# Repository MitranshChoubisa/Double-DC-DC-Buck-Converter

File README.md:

# Double-DC-DC-Buck-Converter
Design of an 48V to 12V to 5V buck converter using LM2576 IC.

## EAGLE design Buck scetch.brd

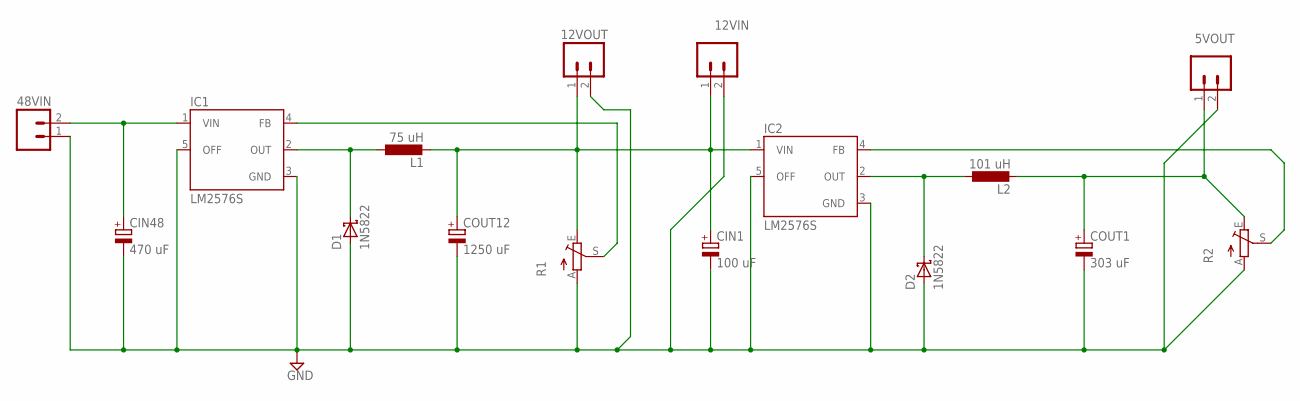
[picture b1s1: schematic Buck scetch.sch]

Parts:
5VOUT, 12VIN, 12VOUT, 48VIN: M02; 02P
CIN1: 100 uF; 140CLH-0810
CIN48: 470 uF; 140CLH-0810
COUT1: 303 uF; 140CLH-0810
COUT12: 1250 uF; 140CLH-0810
D1, D2: 1N5822; DIOAD2120W130L950D530P
IC1, IC2: LM2576S; TO263-5
L1: 75 uH; POWER-CHOKE_WE-TPC
L2: 101 uH; POWER-CHOKE_WE-TPC
R1: 0; B25P
R2: TRIM_EU-B25P; B25P

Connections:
GND: 5VOUT.2, 12VIN.2, 12VOUT.2, 48VIN.1, CIN1.-, CIN48.-, COUT1.-, COUT12.-, D1.A, D2.A, IC1.3 (GND), IC1.5 (OFF), IC2.3 (GND), IC2.5 (OFF), R1.A, R2.A
unnamed: D1.C, IC1.2 (OUT), L1.1
unnamed: 12VIN.1, 12VOUT.1, CIN1.+, COUT12.+, IC2.1 (VIN), L1.2, R1.E
unnamed: IC1.4 (FB), R1.S
unnamed: 48VIN.2, CIN48.+, IC1.1 (VIN)
unnamed: D2.C, IC2.2 (OUT), L2.1
unnamed: 5VOUT.1, COUT1.+, L2.2, R2.E
unnamed: IC2.4 (FB), R2.S

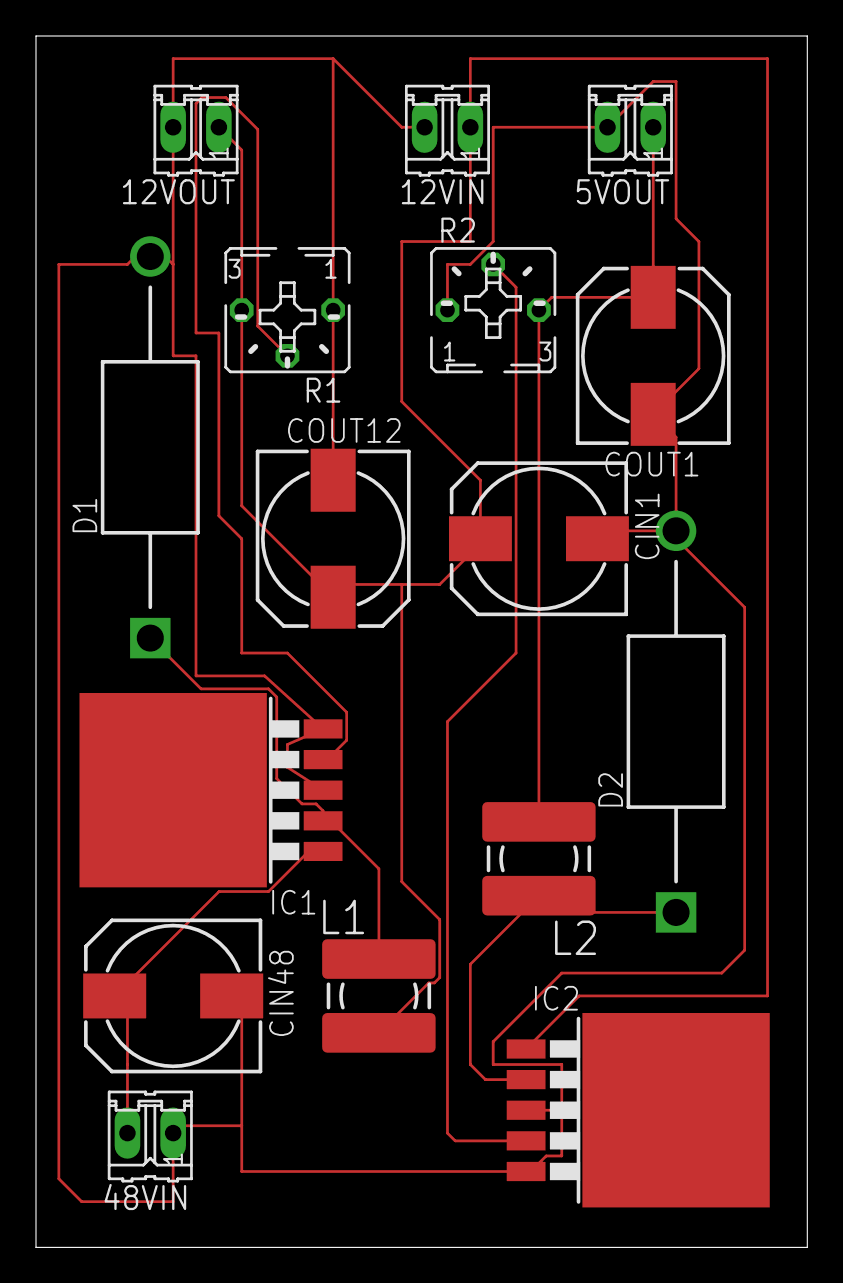
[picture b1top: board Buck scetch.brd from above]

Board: 2 copper layers, 42.9 x 67.3 mm, 16 parts (0 on the bottom side), 8 nets.

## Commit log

2020-06-26 Create 11
2020-06-26 Create 1
